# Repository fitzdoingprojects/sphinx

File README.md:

# sphinx
Sphinx

## Design Requirements
* Powered from 12V, last minimum one night on charge
* 24 LED Buttons (2 sets of 12)
* Audio Playback with Amplified Sound
* Water and Dust Resistant

## Major Components
* MCU - Teensy 3.6
* Buttons - Momentary Metal Push Buttons
* Sound - Speakers, (amplifier?), Sound Playback Controller
* Power - 12V Battery, step-down converters
* Enclosures - Dust/Water Proof, either acrylic or wood
* Cabling - ???

## Questions
* Buttons are momentary? Size requirements? LED color?
	white, 16mm
* Is there already a battery to use?
	or 12v
* Are there already speakers to use?
	get amazon
* How far are buttons from main controller?
* How far apart are buttons from each other?
* What type of mounting structure is available for main controller?
* Should we bring back-ups of components, if so which ones and how many?

## Design Choices
* Exact button type (see BOM)
* Cabling
	* Should each button have a direct wire back to main controller, or should the main controller route to each fin and then seprate wiring to each button.
	* Use pre-made cables (e.g ethernet cable rj45 to each button, or Parallel Port IEEE 1284 cable to each fin), or custom made cables?
* Speakers
	* Either self powered or amplifer plus unpowered speakers. 
	* How loud? 
	* Full range, or additional subwoofer?
* Power 
	* 12V battery, what size? 
	* How to charge?
* Enclosure
	* What type of material
	* How to mount

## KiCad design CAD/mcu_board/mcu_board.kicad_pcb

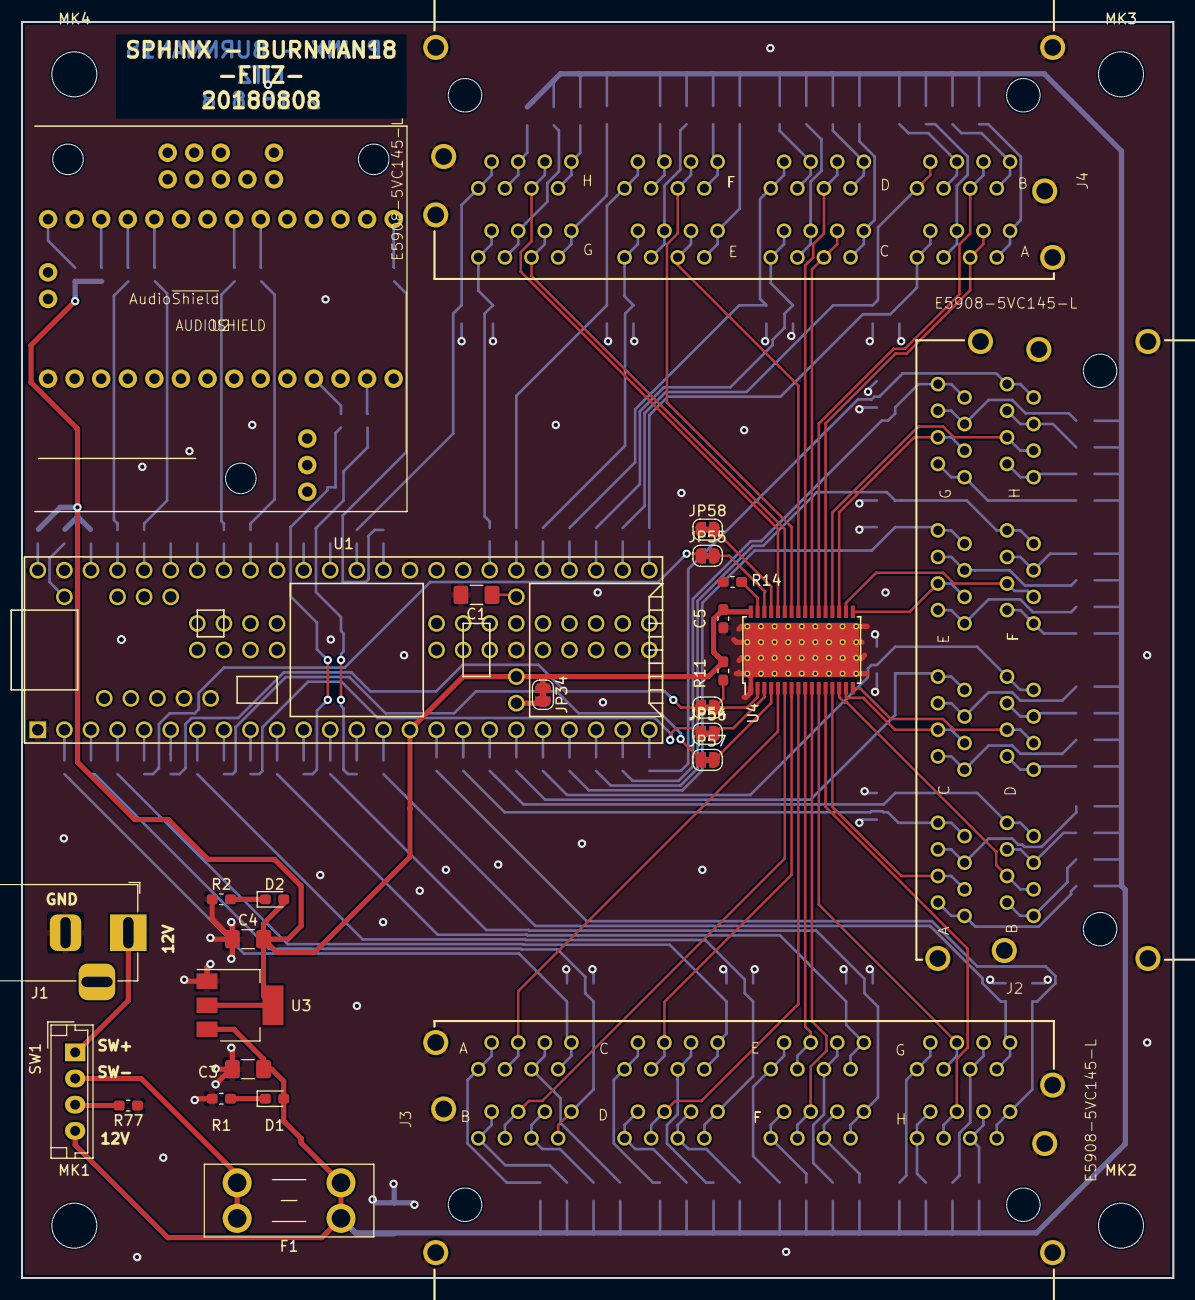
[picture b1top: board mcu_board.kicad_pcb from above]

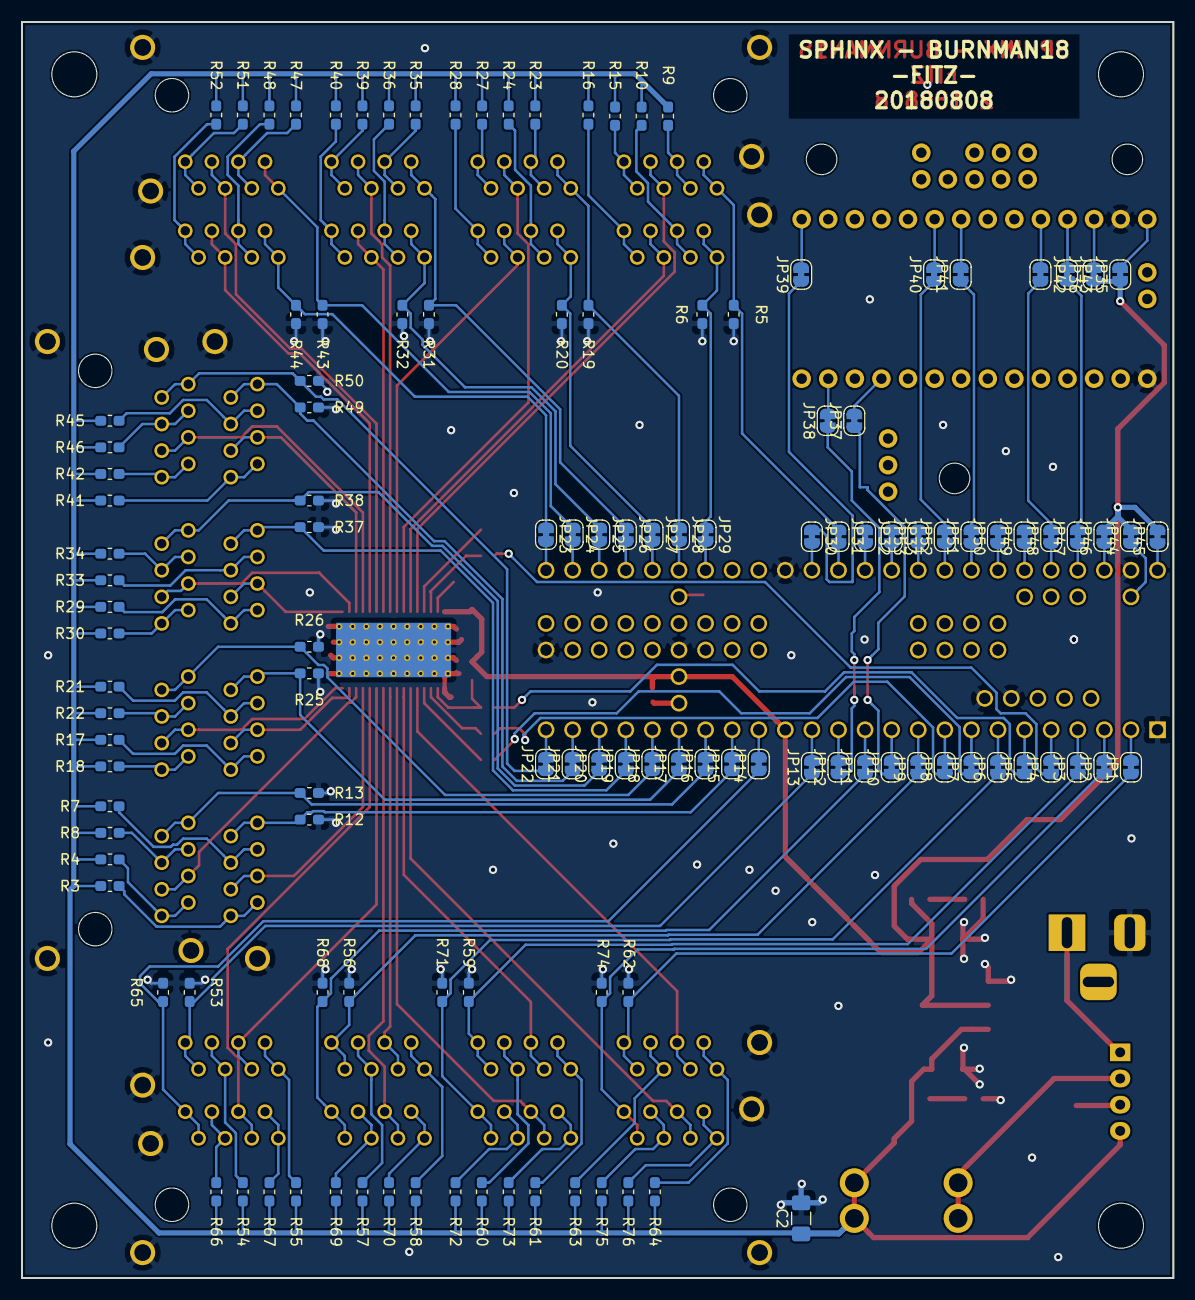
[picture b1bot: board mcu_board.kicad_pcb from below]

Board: 2 copper layers, 110.0 x 120.0 mm, 156 parts (125 on the bottom side), 175 nets.

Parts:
C1: 0.1uF; C_1206_3216Metric_Pad1.42x1.75mm_HandSolder
C2, C3: 22uF; C_1206_3216Metric_Pad1.42x1.75mm_HandSolder
C4: C_Small; C_1206_3216Metric_Pad1.42x1.75mm_HandSolder
C5: 0.1uF; C_0603_1608Metric_Pad1.05x0.95mm_HandSolder
D1, D2: LED_Small; LED_0603_1608Metric_Pad1.05x0.95mm_HandSolder
F1: Fuse_5A; Fuseholder_Blade_Mini_Keystone_3568
J1: 2.1MM BARREL; BarrelJack_Horizontal
J2, J3, J4: E5908-5VC145-L; PULSE_E5908-5VC145-L
JP1, JP2, JP3, JP4, JP5, JP6, JP7, JP8, JP9, JP10, JP11, JP12, JP13, JP14, JP15, JP16, JP17, JP18, JP19, JP20, JP21, JP22, JP23, JP24, JP25, JP26, JP27, JP28, JP29, JP30, JP31, JP32, JP33, JP34, JP35, JP36, JP37, JP38, JP39, JP40, JP41, JP42, JP43, JP44, JP45, JP46, JP47, JP48, JP49, JP50, JP51, JP52, JP53: Jumper_NO_Small; SolderJumper-2_P1.3mm_Bridged_RoundedPad1.0x1.5mm
JP54, JP55, JP56, JP57, JP58: Jumper_NC_Small; SolderJumper-2_P1.3mm_Bridged_RoundedPad1.0x1.5mm
MK1, MK2, MK3, MK4: Mounting_Hole; MountingHole_4.3mm_M4
R1, R2, R11, R14: 10K; R_0603_1608Metric_Pad1.05x0.95mm_HandSolder
R3, R4, R5, R6, R12, R13, R16, R17, R18, R19, R20, R25, R26, R28, R29, R31, R32, R37, R38, R39, R40, R41, R43, R44, R49, R50, R51, R52, R53, R55, R56, R58, R59, R61, R62, R64, R65, R68, R70, R71, R73, R74, R76, R77: 1K; R_0603_1608Metric_Pad1.05x0.95mm_HandSolder
R7, R8, R9, R10, R21, R22, R23, R24, R33, R34, R35, R36, R45, R46, R47, R48, R54, R57, R60, R63, R66, R69, R72, R75: 2.7K; R_0603_1608Metric_Pad1.05x0.95mm_HandSolder
R15, R27, R30, R42, R67: R_L; R_0603_1608Metric_Pad1.05x0.95mm_HandSolder
SW1: SW_SPST_LED; JST_EH_B04B-EH-A_1x04_P2.50mm_Vertical
U1: Teensy3.6; Teensy35_36
U2: AUDIOSHIELD
U3: LM1117-ADJ; SOT-223-3_TabPin2
U4: TLC5947DAP; HTSSOP-32-1EP_6.1x11mm_P0.65mm_EP5.2x11mm_Mask4.11x4.36mm_T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

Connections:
+3V3: C4.2, C5.1, D2.2, JP34.1, JP35.1, JP36.1, JP44.2, JP45.2, JP46.2, R11.2, U1.15, U1.26, U3.2, U4.32
+12V: C2.1, C3.1, D1.2, F1.1, R3.2, R4.2, R7.1, R8.1, R9.1, R10.1, R15.2, R16.2, R17.2, R18.2, R21.1, R22.1, R23.1, R24.1, R27.2, R28.2, R29.2, R30.2, R33.1, R34.1, R35.1, R36.1, R39.2, R40.2, R41.2, R42.2, R45.1, R46.1, R47.1, R48.1, R51.2, R52.2, R54.1, R55.2, R57.1, R58.2, R60.1, R61.2, R63.1, R64.2, R66.1, R67.2, R69.1, R70.2, R72.1, R73.2, R75.1, R76.2, SW1.4, U3.3
/AUDIO_BCLK: JP10.1, JP37.1
/AUDIO_LRCLK: JP43.2, JP47.2
/AUDIO_MCLK: JP12.1, JP38.1
/AUDIO_RX: JP30.1, JP39.1
/AUDIO_SCL: JP41.1, JP51.2
/AUDIO_SDA: JP40.1, JP52.2
/AUDIO_TX: JP42.2, JP48.2
/BLANK: JP5.1, JP54.1
/LED_0: J4.A5, J4.A6, U4.21
/LED_1: J4.B3, J4.B4, U4.22
/LED_2: J4.C5, J4.C6, U4.23
/LED_3: J4.D3, J4.D4, U4.24
/LED_4: J4.E5, J4.E6, U4.25
/LED_5: J4.F3, J4.F4, U4.26
/LED_6: J4.G5, J4.G6, U4.27
/LED_7: J4.H3, J4.H4, U4.28
/LED_8: J2.A5, J2.A6, U4.13
/LED_9: J2.B3, J2.B4, U4.14
/LED_10: J2.C5, J2.C6, U4.15
/LED_11: J2.D3, J2.D4, U4.16
/LED_12: J2.E5, J2.E6, U4.17
/LED_13: J2.F3, J2.F4, U4.18
/LED_14: J2.G5, J2.G6, U4.19
/LED_15: J2.H3, J2.H4, U4.20
/LED_16: J3.A5, J3.A6, U4.5
/LED_17: J3.B3, J3.B4, U4.6
/LED_18: J3.C5, J3.C6, U4.7
/LED_19: J3.D3, J3.D4, U4.8
/LED_20: J3.E5, J3.E6, U4.9
/LED_21: J3.F3, J3.F4, U4.10
/LED_22: J3.G5, J3.G6, U4.11
/LED_23: J3.H3, J3.H4, U4.12
/SCLK: JP8.1, JP56.1
/SIN: JP7.1, JP57.1
/SW_0: J4.A1, J4.A2, JP23.1, R44.2
/SW_1: J4.B7, J4.B8, JP24.1, R43.2
/SW_2: J4.C1, J4.C2, JP25.1, R32.2
/SW_3: J4.D7, J4.D8, JP26.1, R31.2
/SW_4: J4.E1, J4.E2, JP27.1, R20.2
/SW_5: J4.F7, J4.F8, JP28.1, R19.2
/SW_6: J4.G1, J4.G2, JP29.1, R6.2
/SW_7: J4.H7, J4.H8, JP31.1, R5.2
/SW_8: J2.A1, J2.A2, JP15.1, R12.2
/SW_9: J2.B7, J2.B8, JP16.1, R13.2
/SW_10: J2.C1, J2.C2, JP17.1, R25.2
/SW_11: J2.D7, J2.D8, JP18.1, R26.2
/SW_12: J2.E1, J2.E2, JP19.1, R37.2
/SW_13: J2.F7, J2.F8, JP20.1, R38.2
/SW_14: J2.G1, J2.G2, JP21.1, R49.2
/SW_15: J2.H7, J2.H8, JP22.1, R50.2
/SW_16: J3.A1, J3.A2, JP1.1, R62.2
/SW_17: J3.B7, J3.B8, JP2.1, R74.2
/SW_18: J3.C1, J3.C2, JP3.1, R59.2
/SW_19: J3.D7, J3.D8, JP6.1, R71.2
/SW_20: J3.E1, J3.E2, JP9.1, R56.2
/SW_21: J3.F7, J3.F8, JP11.1, R68.2
/SW_22: J3.G1, J3.G2, JP13.1, R53.2
/SW_23: J3.H7, J3.H8, JP14.1, R65.2
/XLAT: JP4.1, JP55.1
GND: C1.2, C2.2, C3.2, C4.1, C5.2, J1.2, J2.P1, J2.P2, J2.P3, J2.P4, J2.P5, J2.P6, J3.P1, J3.P2, J3.P3, J3.P4, J3.P5, J3.P6, J4.P1, J4.P2, J4.P3, J4.P4, J4.P5, J4.P6, R1.1, R2.1, R5.1, R6.1, R12.1, R13.1, R14.1, R19.1, R20.1, R25.1, R26.1, R31.1, R32.1, R37.1, R38.1, R43.1, R44.1, R49.1, R50.1, R53.1, R56.1, R59.1, R62.1, R65.1, R68.1, R71.1, R74.1, R77.1, U1.1, U1.27, U1.39, U1.52, U1.61, U1.62, U1.74, U2.G, U2.GND, U3.1, U4.1, U4.33
unnamed: C1.1, U1.29
unnamed: D1.1, R1.2
unnamed: D2.1, R2.2
unnamed: F1.2, SW1.2
unnamed: J1.1, SW1.1
unnamed: J2.A3, J2.A4, R7.2
unnamed: J2.A7, J2.A8, R3.1
unnamed: J2.B1, J2.B2, R4.1
unnamed: J2.B5, J2.B6, R8.2
unnamed: J2.C3, J2.C4, R21.2
unnamed: J2.C7, J2.C8, R17.1
unnamed: J2.D1, J2.D2, R18.1
unnamed: J2.D5, J2.D6, R22.2
unnamed: J2.E3, J2.E4, R33.2
unnamed: J2.E7, J2.E8, R29.1
unnamed: J2.F1, J2.F2, R30.1
unnamed: J2.F5, J2.F6, R34.2
unnamed: J2.G3, J2.G4, R45.2
unnamed: J2.G7, J2.G8, R41.1
unnamed: J2.H1, J2.H2, R42.1
unnamed: J2.H5, J2.H6, R46.2
unnamed: J3.A3, J3.A4, R63.2
unnamed: J3.A7, J3.A8, R64.1
unnamed: J3.B1, J3.B2, R76.1
unnamed: J3.B5, J3.B6, R75.2
unnamed: J3.C3, J3.C4, R60.2
unnamed: J3.C7, J3.C8, R61.1
unnamed: J3.D1, J3.D2, R73.1
unnamed: J3.D5, J3.D6, R72.2
unnamed: J3.E3, J3.E4, R57.2
unnamed: J3.E7, J3.E8, R58.1
unnamed: J3.F1, J3.F2, R70.1
unnamed: J3.F5, J3.F6, R69.2
unnamed: J3.G3, J3.G4, R54.2
unnamed: J3.G7, J3.G8, R55.1
unnamed: J3.H1, J3.H2, R67.1
unnamed: J3.H5, J3.H6, R66.2
unnamed: J4.A3, J4.A4, R48.2
unnamed: J4.A7, J4.A8, R52.1
unnamed: J4.B1, J4.B2, R51.1
unnamed: J4.B5, J4.B6, R47.2
unnamed: J4.C3, J4.C4, R36.2
unnamed: J4.C7, J4.C8, R40.1
unnamed: J4.D1, J4.D2, R39.1
unnamed: J4.D5, J4.D6, R35.2
unnamed: J4.E3, J4.E4, R24.2
unnamed: J4.E7, J4.E8, R28.1
unnamed: J4.F1, J4.F2, R27.1
unnamed: J4.F5, J4.F6, R23.2
unnamed: J4.G3, J4.G4, R10.2
unnamed: J4.G7, J4.G8, R16.1
unnamed: J4.H1, J4.H2, R15.1
unnamed: J4.H5, J4.H6, R9.2
unnamed: JP1.2, U1.2
unnamed: JP2.2, U1.3
unnamed: JP3.2, U1.4
unnamed: JP4.2, U1.5
unnamed: JP5.2, U1.6
unnamed: JP6.2, U1.7
unnamed: JP7.2, U1.8
unnamed: JP8.2, U1.9
unnamed: JP9.2, U1.10
unnamed: JP10.2, U1.11
unnamed: JP11.2, U1.12
unnamed: JP12.2, U1.13
unnamed: JP13.2, U1.14
unnamed: JP14.2, U1.16
unnamed: JP15.2, U1.17
unnamed: JP16.2, U1.18
unnamed: JP17.2, U1.19
unnamed: JP18.2, U1.20
unnamed: JP19.2, U1.21
unnamed: JP20.2, U1.22
unnamed: JP21.2, U1.23
unnamed: JP22.2, U1.24
unnamed: JP23.2, U1.30
unnamed: JP24.2, U1.31
unnamed: JP25.2, U1.32
unnamed: JP26.2, U1.33
unnamed: JP27.2, U1.34
unnamed: JP28.2, U1.35
unnamed: JP29.2, U1.36
unnamed: JP30.2, U1.40
unnamed: JP31.2, U1.41
unnamed: JP32.2, U1.42
unnamed: JP33.2, U1.43
unnamed: JP34.2, U1.25
unnamed: JP35.2, U2.5V
unnamed: JP36.2, U2.3V
unnamed: JP37.2, U2.9
unnamed: JP38.2, U2.11
unnamed: JP39.2, U2.13
unnamed: JP40.2, U2.18
unnamed: JP41.2, U2.19
unnamed: JP42.1, U2.22
unnamed: JP43.1, U2.23
unnamed: JP44.1, U1.54
unnamed: JP45.1, U1.53
unnamed: JP46.1, U1.51
unnamed: JP47.1, U1.50
unnamed: JP48.1, U1.49
unnamed: JP49.1, U1.48
unnamed: JP50.1, U1.47
unnamed: JP51.1, U1.46
unnamed: JP52.1, U1.45
unnamed: JP53.1, U1.44
unnamed: JP54.2, R11.1, U4.2
unnamed: JP55.2, U4.30
unnamed: JP56.2, U4.3
unnamed: JP57.2, U4.4
unnamed: JP58.2, U4.29
unnamed: R14.2, U4.31
unnamed: R77.2, SW1.3

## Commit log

2018-07-12 adds BOM and updates README
2018-07-12 fixes readme formating
2018-07-13 updated BOM
2018-07-29 adds KiCAD files
2018-07-30 completes most wiring for MCU
2018-08-05 adds libs and firmwares
2018-08-08 updates layout
2018-08-09 finishes most routing
2018-08-09 finish all routing but GND
2018-08-11 FINAL COMMIT FOR GERBERS 180808
